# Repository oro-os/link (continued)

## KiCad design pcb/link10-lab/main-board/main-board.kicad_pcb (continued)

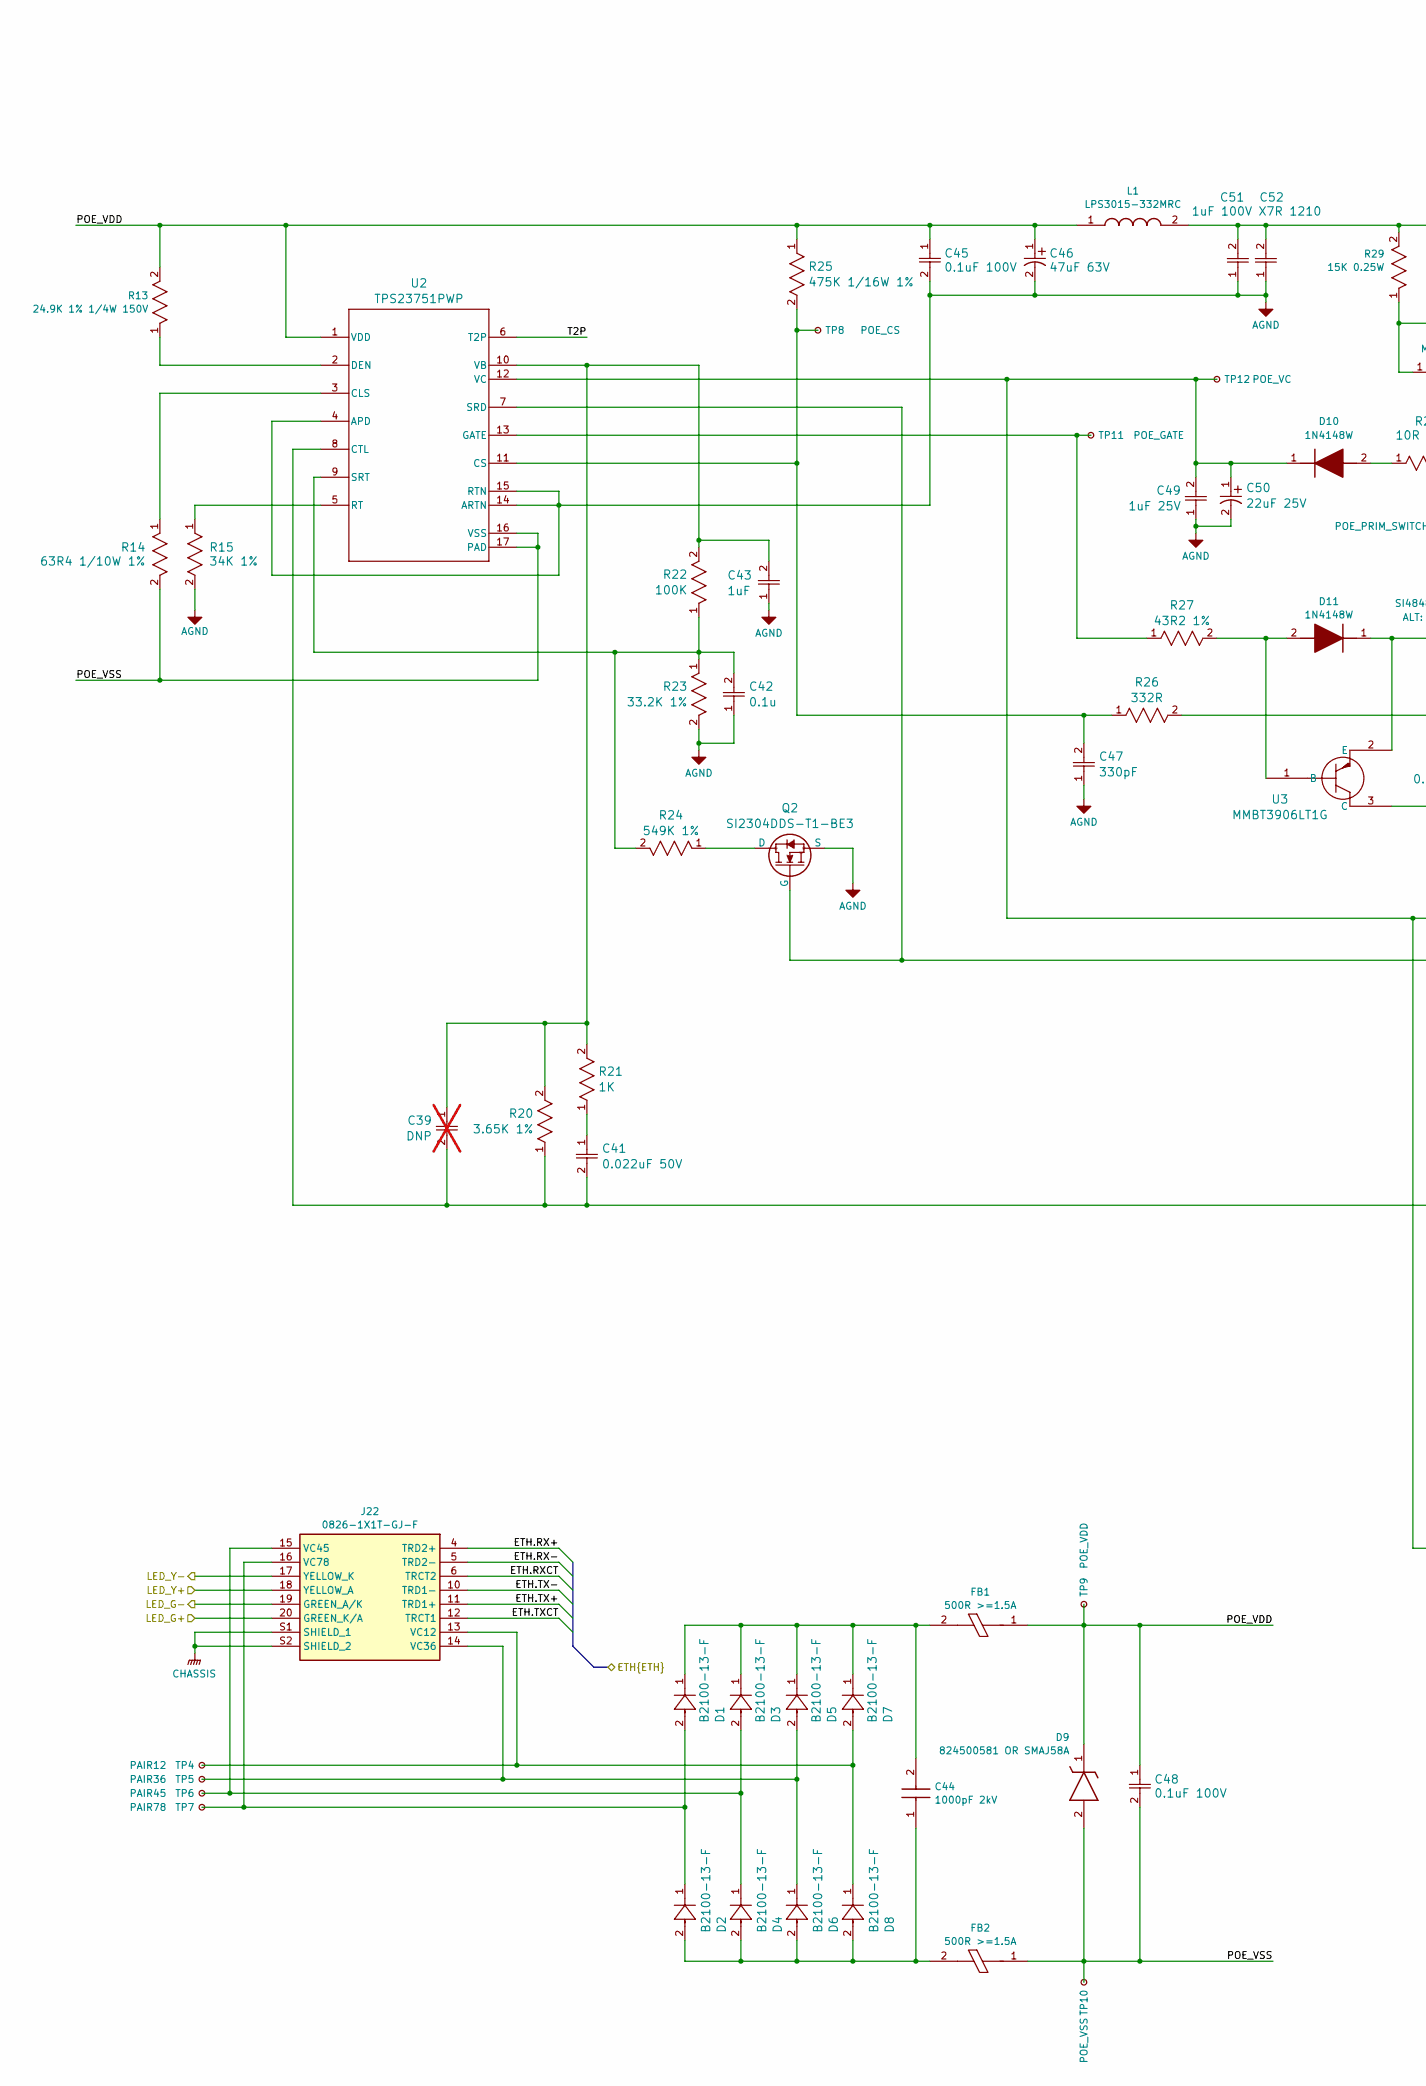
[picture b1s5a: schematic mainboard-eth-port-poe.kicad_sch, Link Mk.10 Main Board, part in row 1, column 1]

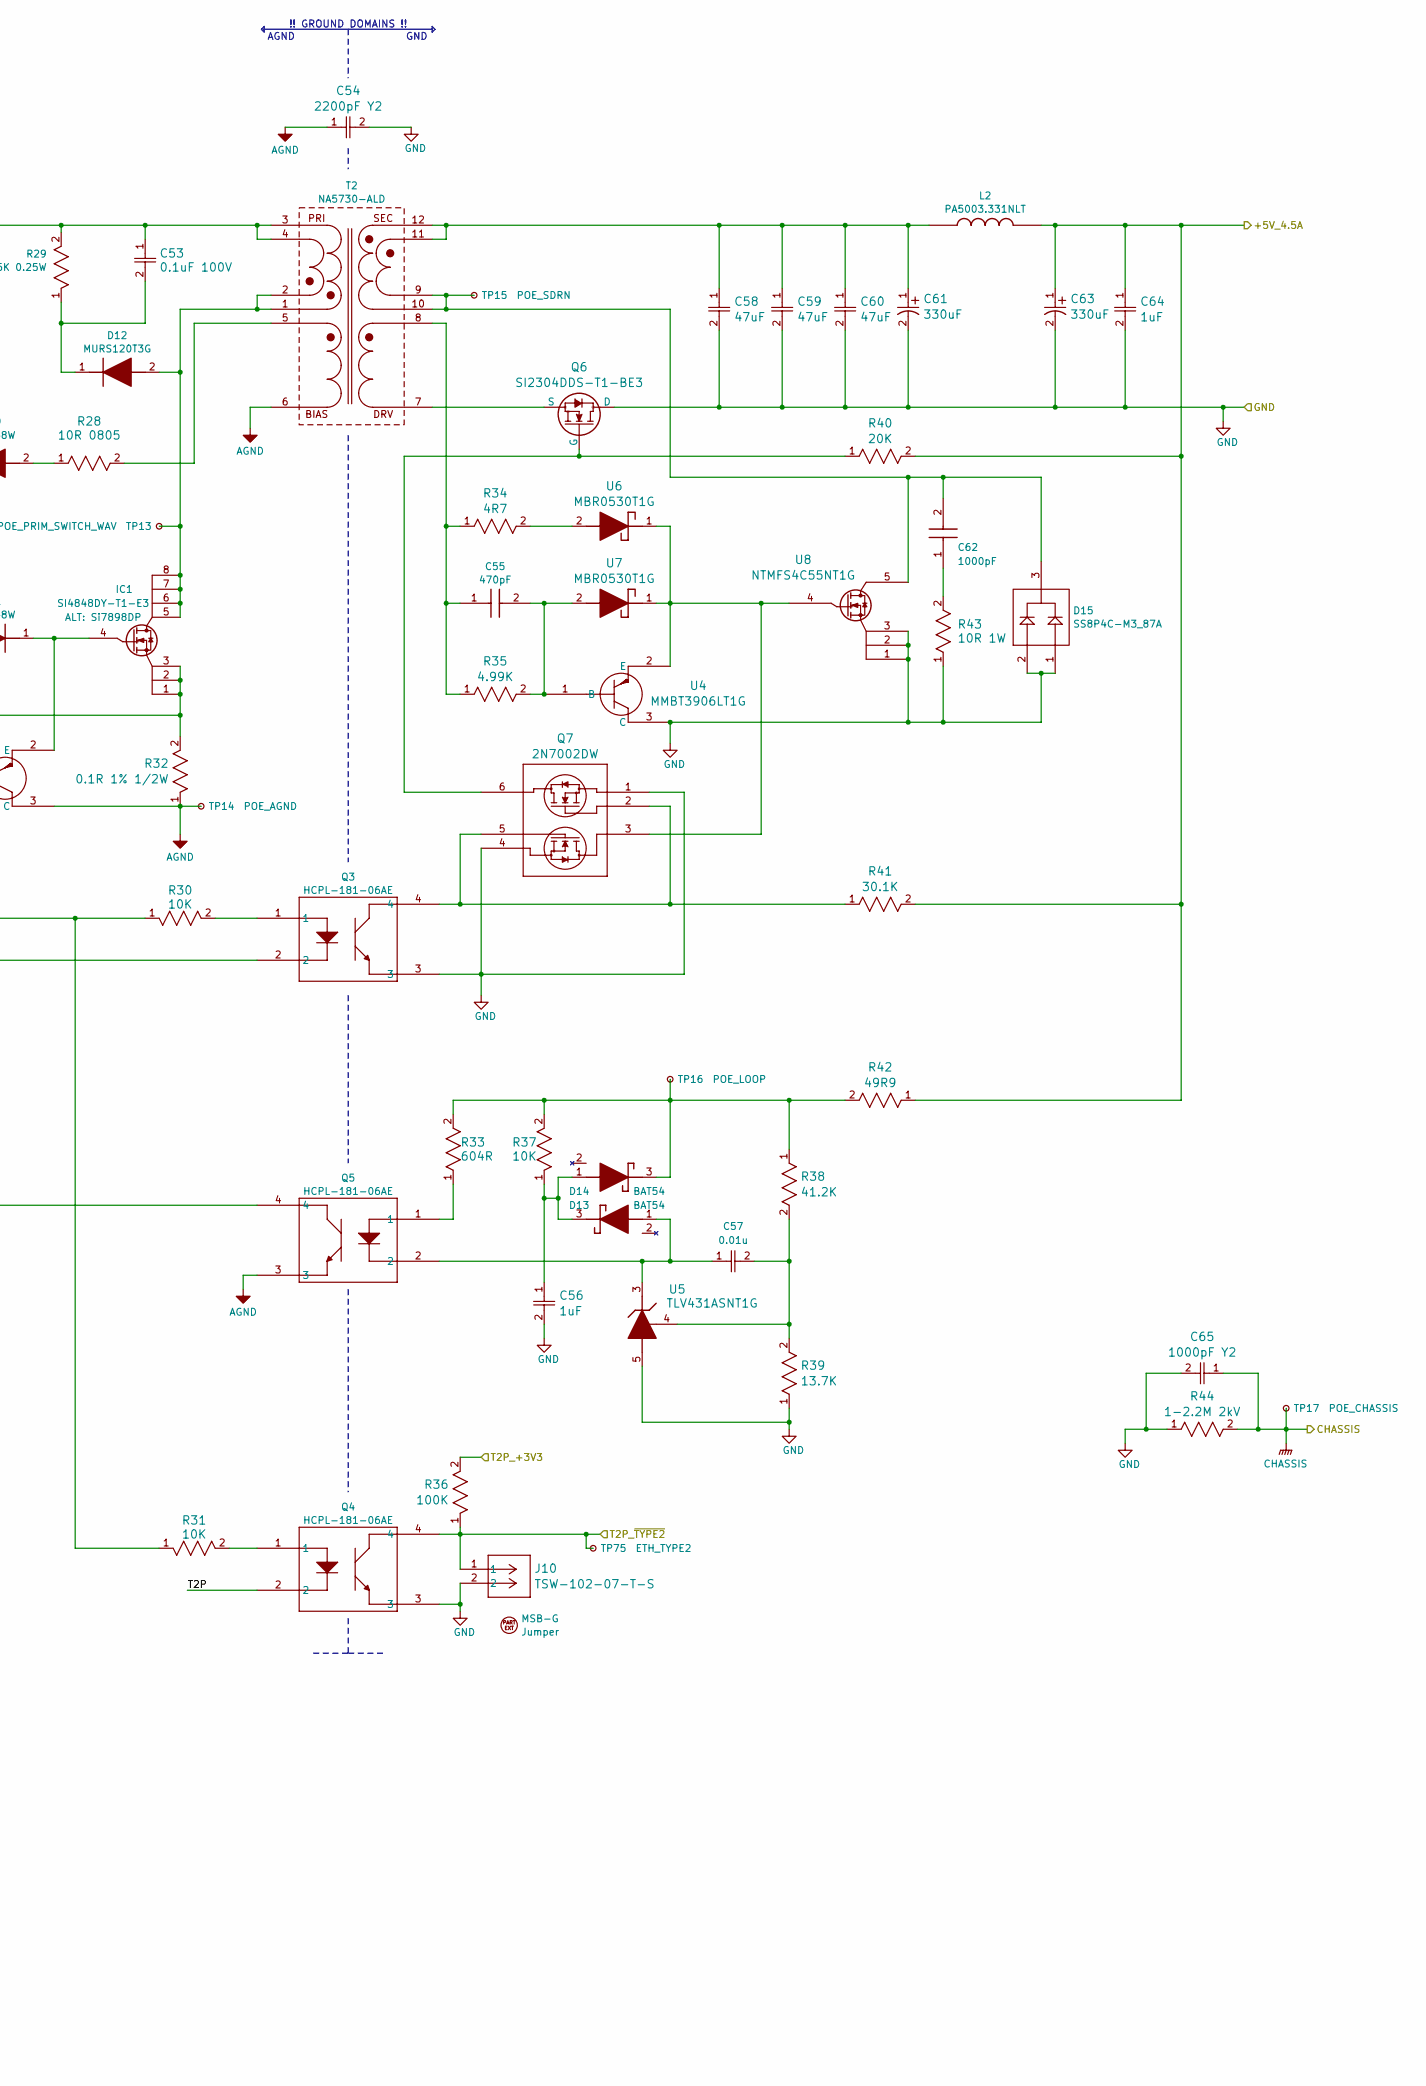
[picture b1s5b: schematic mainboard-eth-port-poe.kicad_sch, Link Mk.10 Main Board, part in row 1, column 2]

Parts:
C39: DNP; C_0603_1608Metric; not fitted
C41: 0.022uF 50V; OP_00069; Mouser P/N 810-CGA3E2X7R1H223K; Digi-Key P/N 445-5663-1-ND, 445-5663-2-ND, 445-5663-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
C42: 0.1u; OP_0001Y; DigiKey ID 587-MSAST1L3YB5104KFNA01CT-ND
C43: 1uF; OP_0005T
C44: 1000pF 2kV; OP_0000R; Manufacturer_Part_Number 885342210004; Mouser Part Number 710-885342210004
C45, C48, C53: 0.1uF 100V; OP_0005M; Mouser P/N 187-CL21B104KCFSFNE; Digi-Key P/N 1276-2923-1-ND, 1276-2923-2-ND, 1276-29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
C46: 47uF 63V; OP_0005N
C47: 330pF; OP_00068
C49: 1uF 25V; OP_0005T
C50: 22uF 25V; OP_0005V
C51, C52: 1uF 100V X7R 1210; OP_0005L
C54: 2200pF Y2; OP_0006U; Mouser P/N 710-8853522130151; Digi-Key P/N 732-8853522130151CT-ND, 732-88535221301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
C55: 470pF; OP_0006Q; Manufacturer_Part_Number C0603C471K5RAC; Mouser Part Number 80-C0603C471K5RAC
C56, C64: 1uF; OP_00001; Mouser P/N 581-0603YD105K; Digi-Key P/N 478-KGM15BR51C105KTCT-ND, 478-KGM15BR51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
C57: 0.01u; OP_0005C; Manufacturer_Part_Number C0603C103J2RECAUTO7411; Mouser Part Number 80-C0603C103J2REAULR
C58, C59, C60: 47uF; OP_0006G; Mouser P/N 963-LMK325BJ476KMHP; Digi-Key P/N 587-6341-1-ND, 587-6341-2-ND, 587-6341-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
C61, C63: 330uF; OP_0006H; Mouser P/N 667-EEE-FK0J331XP; Digi-Key P/N PCE3768CT-ND, PCE3768DKR-ND, PCE3768TR-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
C62: 1000pF; OP_0000R; Manufacturer_Part_Number 885342210004; Mouser Part Number 710-885342210004
C65: 1000pF Y2; OP_0006V; Mouser P/N 710-8853522130111; Digi-Key P/N 732-8853522130111CT-ND, 732-88535221301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
D1, D2, D3, D4, D5, D6, D7, D8: B2100-13-F; OP_0005E
D9: 824500581 OR SMAJ58A; OP_0005G; Manufacturer_Part_Number 824500581; Mouser Part Number 710-824500581
D10, D11: 1N4148W; OP_0005S; Manufacturer_Part_Number 1N4148W; Mouser Part Number 637-1N4148W
D12: MURS120T3G; OP_0005P; Manufacturer_Part_Number MURS120T3G; Mouser Part Number 863-MURS120T3G
D13, D14: BAT54; OP_0006I; Manufacturer_Part_Number BAT54; Mouser Part Number 637-BAT54
D15: SS8P4C-M3_87A; OP_0006E; Manufacturer_Part_Number SS8P4C-M3/87A; Mouser Part Number 625-SS8P4C-M3/87A
EXT2: MSB-G; Mouser P/N 737-MSB-G; Digi-Key P/N 2057-MSB-G-ND
FB1, FB2: 500R >=1.5A; OP_0005F; Manufacturer_Part_Number NFZ2MSD501SZ10L; Mouser Part Number 81-NFZ2MSD501SZ10L
IC1: SI4848DY-T1-E3; OP_0005R; Manufacturer_Part_Number SI4848DY-T1-E3; Mouser Part Number 781-SI4848DY-T1-E3
J10: TSW-102-07-T-S; OP_00079; Mouser P/N 200-TSW10207TS; Digi-Key P/N 612-TSW-102-07-T-S-ND
J22: 0826-1X1T-GJ-F; OP_0007O; Manufacturer_Part_Number 0826-1X1T-GJ-F; Mouser Part Number 530-0826-1X1T-GJ-F
L1: LPS3015-332MRC; OP_0005I; Manufacturer_Part_Number LPS3015-332MRC; Mouser Part Number 994-LPS3015-332MRC
L2: PA5003.331NLT; OP_0006F; Mouser P/N 673-PA5003.331NLT; Digi-Key P/N 553-4080-1-ND, 553-4080-2-ND, 553-4080-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
Q2, Q6: SI2304DDS-T1-BE3; OP_00063
Q3, Q4, Q5: HCPL-181-06AE; OP_00062; Manufacturer_Part_Number HCPL-181-06AE; Mouser Part Number 630-HCPL-181-06AE
Q7: 2N7002DW; OP_0006D; Mouser P/N 512-2N7002DW; Digi-Key P/N 2N7002DWCT-ND, 2N7002DWDKR-ND, 2N7002DW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
R13: 24.9K 1% 1/4W 150V; OP_0005H; Manufacturer_Part_Number CR1206-FX-2492ELF; Mouser Part Number 652-CR1206FX-2492ELF
R14: 63R4 1/10W 1%; OP_0005W
R15: 34K 1%; OP_0005X
R20: 3.65K 1%; OP_0006A; Mouser P/N 71-CRCW0603-3.65K-E3; Digi-Key P/N 541-3.65KHCT-ND, 541-3.65KHDKR-ND, 541-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
R21: 1K; OP_0003D
R22, R36: 100K; OP_00066
R23: 33.2K 1%; OP_00065
R24: 549K 1%; OP_00064; Mouser P/N 71-CRCW0603549KFKEAH; Digi-Key P/N CRCW0603549KFKEAHP-ND
R25: 475K 1/16W 1%; OP_0005Q; Manufacturer_Part_Number RC0603FR-07475KL; Mouser Part Number 603-RC0603FR-07475KL
R26: 332R; OP_00067
R27: 43R2 1%; OP_0005Y
R28: 10R 0805; OP_0005U
R29: 15K 0.25W; OP_0005O; Manufacturer_Part_Number RK73H2BTTD1502F; Mouser Part Number 660-RK73H2BTTD1502F
R30, R31, R37: 10K; OP_00021; DigiKey ID RMCF0402FT10K0CT-ND
R32: 0.1R 1% 1/2W; OP_00060
R33: 604R; OP_0006K; Mouser P/N 667-ERA-3AEB6040V, ERA-3AEB6040V; Digi-Key P/N P604DBCT-ND, P604DBDKR-ND, P604DBTR-ND
R34: 4R7; OP_0006O; Mouser P/N 594-MCT06030C4708FP5; Digi-Key P/N 749-1657-1-ND, 749-1657-2-ND, 749-1657-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
R35: 4.99K; OP_0006P; Mouser P/N 603-RT0603BRD074K99L; Digi-Key P/N YAG1678CT-ND, YAG1678DKR-ND, YAG1678TR-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
R38: 41.2K; OP_0006J; Mouser P/N 594-MCT06030C4122FP5; Digi-Key P/N 749-MCT06030C4122FP500CT-ND, 749-MCT060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
R39: 13.7K; OP_0006M; Mouser P/N 594-MCT0603MD1372DP5; Digi-Key P/N 749-MCT0603MD1372DP500CT-ND, 749-MCT060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
R40: 20K; OP_0006R; Mouser P/N 603-RT0603BRD0720KL; Digi-Key P/N YAG1582CT-ND, YAG1582DKR-ND, YAG1582TR-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
R41: 30.1K; OP_0006S; Mouser P/N 279-CPF0603F30K1C1; Digi-Key P/N A102260CT-ND, A102260DKR-ND, A102260TR-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
R42: 49R9; OP_00023; Mouser P/N 603-RT0402FRE0749R9L; Mouser URL null
R43: 10R 1W; OP_0006N; Mouser P/N 754-CPA2512Q10R0FST; Digi-Key P/N CPA25Q10.0CT-ND, CPA25Q10.0DKR-ND, CPA2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
R44: 1-2.2M 2kV; OP_0006W; Mouser P/N 652-CHV2512JW105ELF; Digi-Key P/N 118-CHV2512-JW-105ELFCT-ND, 118-CHV2512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
T2: NA5730-ALD; OP_0005J; Manufacturer_Part_Number NA5730-ALD; Mouser Part Number 994-NA5730-ALD
TP4: PAIR12; TestPoint_Pad_2.0x2.0mm
TP5: PAIR36; TestPoint_Pad_2.0x2.0mm
TP6: PAIR45; TestPoint_Pad_2.0x2.0mm
TP7: PAIR78; TestPoint_Pad_2.0x2.0mm
TP8: POE_CS; TestPoint_Pad_2.0x2.0mm
TP9: POE_VDD; TestPoint_Pad_2.0x2.0mm
TP10: POE_VSS; TestPoint_Pad_2.0x2.0mm
TP11: POE_GATE; TestPoint_Pad_2.0x2.0mm
TP12: POE_VC; TestPoint_Pad_2.0x2.0mm
TP13: POE_PRIM_SWITCH_WAV; TestPoint_Pad_2.0x2.0mm
TP14: POE_AGND; TestPoint_Pad_2.0x2.0mm
TP15: POE_SDRN; TestPoint_Pad_2.0x2.0mm
TP16: POE_LOOP; TestPoint_Pad_2.0x2.0mm
TP17: POE_CHASSIS; TestPoint_Pad_2.0x2.0mm
TP75: ETH_TYPE2; TestPoint_Pad_D1.0mm
U2: TPS23751PWP; OP_00057
U3, U4: MMBT3906LT1G; OP_0005Z
U5: TLV431ASNT1G; OP_0006L; Mouser P/N 863-TLV431ASNT1G; Digi-Key P/N TLV431ASNT1GOSCT-ND, TLV431ASNT1GOSDKR-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
U6, U7: MBR0530T1G; OP_0006B; Mouser P/N 863-MBR0530T1G; Digi-Key P/N MBR0530T1GOSCT-ND, MBR0530T1GOSDKR-ND, 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
U8: NTMFS4C55NT1G; OP_0006C; Mouser P/N 863-NTMFS4C55NT1G; Digi-Key P/N 488-NTMFS4C55NT1GCT-ND, 488-NTMFS4C55NT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

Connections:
+3V3_BASE: R36.2; also elsewhere on the board
+5V: C63.1, C64.1, L2.2, R40.2, R41.2, R42.1; also elsewhere on the board
/Baseboard/ETH_IS_TYPE2: J10.1, Q4.4, R36.1, TP75.1 (1_1); also elsewhere on the board
/CHASSIS: C65.1, J22.S1 (SHIELD_1), J22.S2 (SHIELD_2), R44.2, TP17.1 (1_1); also elsewhere on the board
/Ethernet Port + PoE/AGND: C42.1, C43.1, C45.2, C46.2, C47.1, C49.1, C50.2, C51.1, C52.1, C54.1, Q2.2 (S), Q5.3, R15.2, R23.2, R32.1, T2.6 (BIAS_2), TP14.1 (1_1), U2.4 (APD), U2.14 (ARTN), U2.15 (RTN), U3.3 (C)
/Ethernet Port + PoE/ETH.RX+: J22.4 (TRD2+); also elsewhere on the board
/Ethernet Port + PoE/ETH.RX-: J22.5 (TRD2-); also elsewhere on the board
/Ethernet Port + PoE/ETH.TX+: J22.11 (TRD1+); also elsewhere on the board
/Ethernet Port + PoE/ETH.TX-: J22.10 (TRD1-); also elsewhere on the board
/Ethernet Port + PoE/ETH.TXCT: J22.6 (TRCT2), J22.12 (TRCT1); also elsewhere on the board
/Ethernet Port + PoE/LED_G+: J22.20 (GREEN_K/A); also elsewhere on the board
/Ethernet Port + PoE/LED_G-: J22.19 (GREEN_A/K); also elsewhere on the board
/Ethernet Port + PoE/LED_Y+: J22.18 (YELLOW_A); also elsewhere on the board
/Ethernet Port + PoE/LED_Y-: J22.17 (YELLOW_K); also elsewhere on the board
/Ethernet Port + PoE/POE_VDD: C45.1, C46.1, C48.1, D9.1 (K), FB1.1, L1.1, R13.2, R25.1, TP9.1 (1_1), U2.1 (VDD)
/Ethernet Port + PoE/POE_VSS: C48.2, D9.2 (A), FB2.1, R14.2, TP10.1 (1_1), U2.16 (VSS), U2.17 (PAD)
/Ethernet Port + PoE/T2P: Q4.2, U2.6 (T2P)
GND: C54.2, C56.2, C58.2, C59.2, C60.2, C61.2, C63.2, C64.2, C65.2, D15.1 (A_1), D15.2 (A_2), J10.2, Q3.3, Q4.3, Q6.3 (D), Q7.1, Q7.4, R39.1, R43.1, R44.1, U4.3 (C), U5.5 (ANODE), U8.1 (SOURCE), U8.2 (SOURCE), U8.3 (SOURCE); also elsewhere on the board
unnamed: C41.1, R21.1
unnamed: C44.1, D2.2, D4.2, D6.2, D8.2, FB2.2
unnamed: C44.2, D1.1, D3.1, D5.1, D7.1, FB1.2
unnamed: C62.1, R43.2
unnamed: D10.2 (A), R28.1
unnamed: C49.2, C50.1, D10.1 (K), R30.1, R31.1, TP12.1 (1_1), U2.12 (VC)
unnamed: D11.2 (A), R27.2, U3.1 (B)
unnamed: D11.1 (K), IC1.4 (G), U3.2 (E)
unnamed: D12.2 (A), IC1.5 (D_1), IC1.6 (D_2), IC1.7 (D_3), IC1.8 (D_4), T2.1 (PRI_1_1), T2.2 (PRI_2_1), TP13.1 (1_1)
unnamed: C53.2, D12.1 (K), R29.1
unnamed: C57.1, D13.1 (A), Q5.2, U5.3 (CATHODE)
unnamed: C56.1, D13.3 (K), D14.1 (A), R37.1
unnamed: D14.3 (K), R33.2, R37.2, R38.1, R42.2, TP16.1 (1_1)
unnamed: C62.2, D15.3 (K), T2.9 (SEC_1_1), T2.10 (SEC_2_1), TP15.1 (1_1), U8.5 (DRAIN)
unnamed: IC1.1 (S_1), IC1.2 (S_2), IC1.3 (S_3), R26.2, R32.2
unnamed: D7.2, D8.1, J22.13 (VC12), TP4.1 (1_1)
unnamed: D5.2, D6.1, J22.14 (VC36), TP5.1 (1_1)
unnamed: D3.2, D4.1, J22.15 (VC45), TP6.1 (1_1)
unnamed: D1.2, D2.1, J22.16 (VC78), TP7.1 (1_1)
unnamed: Q2.3 (D), R24.1
unnamed: Q2.1 (G), Q3.2, U2.7 (SRD)
unnamed: Q3.1, R30.2
unnamed: Q3.4, Q7.2, Q7.5, R41.1
unnamed: Q4.1, R31.2
unnamed: Q5.1, R33.1
unnamed: Q6.1 (G), Q7.6, R40.1
unnamed: Q6.2 (S), T2.7 (DRIVE_1)
unnamed: R28.2, T2.5 (BIAS_1)
unnamed: C55.1, R34.1, R35.1, T2.8 (DRIVE_2)
unnamed: C51.2, C52.2, C53.1, L1.2, R29.2, T2.3 (PRI_1_2), T2.4 (PRI_2_2)
unnamed: C58.1, C59.1, C60.1, C61.1, L2.1, T2.11 (SEC_1_2), T2.12 (SEC_2_2)
unnamed: R14.1, U2.3 (CLS)
unnamed: C47.2, R25.2, R26.1, TP8.1 (1_1), U2.11 (CS)
unnamed: C39.2, C41.2, Q5.4, R20.1, U2.8 (CTL)
unnamed: R13.1, U2.2 (DEN)
unnamed: R27.1, TP11.1 (1_1), U2.13 (GATE)
unnamed: R15.1, U2.5 (RT)
unnamed: C42.2, R22.1, R23.1, R24.2, U2.9 (SRT)
unnamed: C39.1, C43.2, R20.2, R21.2, R22.2, U2.10 (VB)
unnamed: C55.2, R35.2, U4.1 (B), U7.2 (ANODE)
unnamed: Q7.3, U4.2 (E), U6.1 (CATHODE), U7.1 (CATHODE), U8.4 (GATE)
unnamed: C57.2, R38.2, R39.2, U5.4 (REFERENCE)
unnamed: R34.2, U6.2 (ANODE)

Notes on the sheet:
GND
!! GROUND DOMAINS !!
AGND

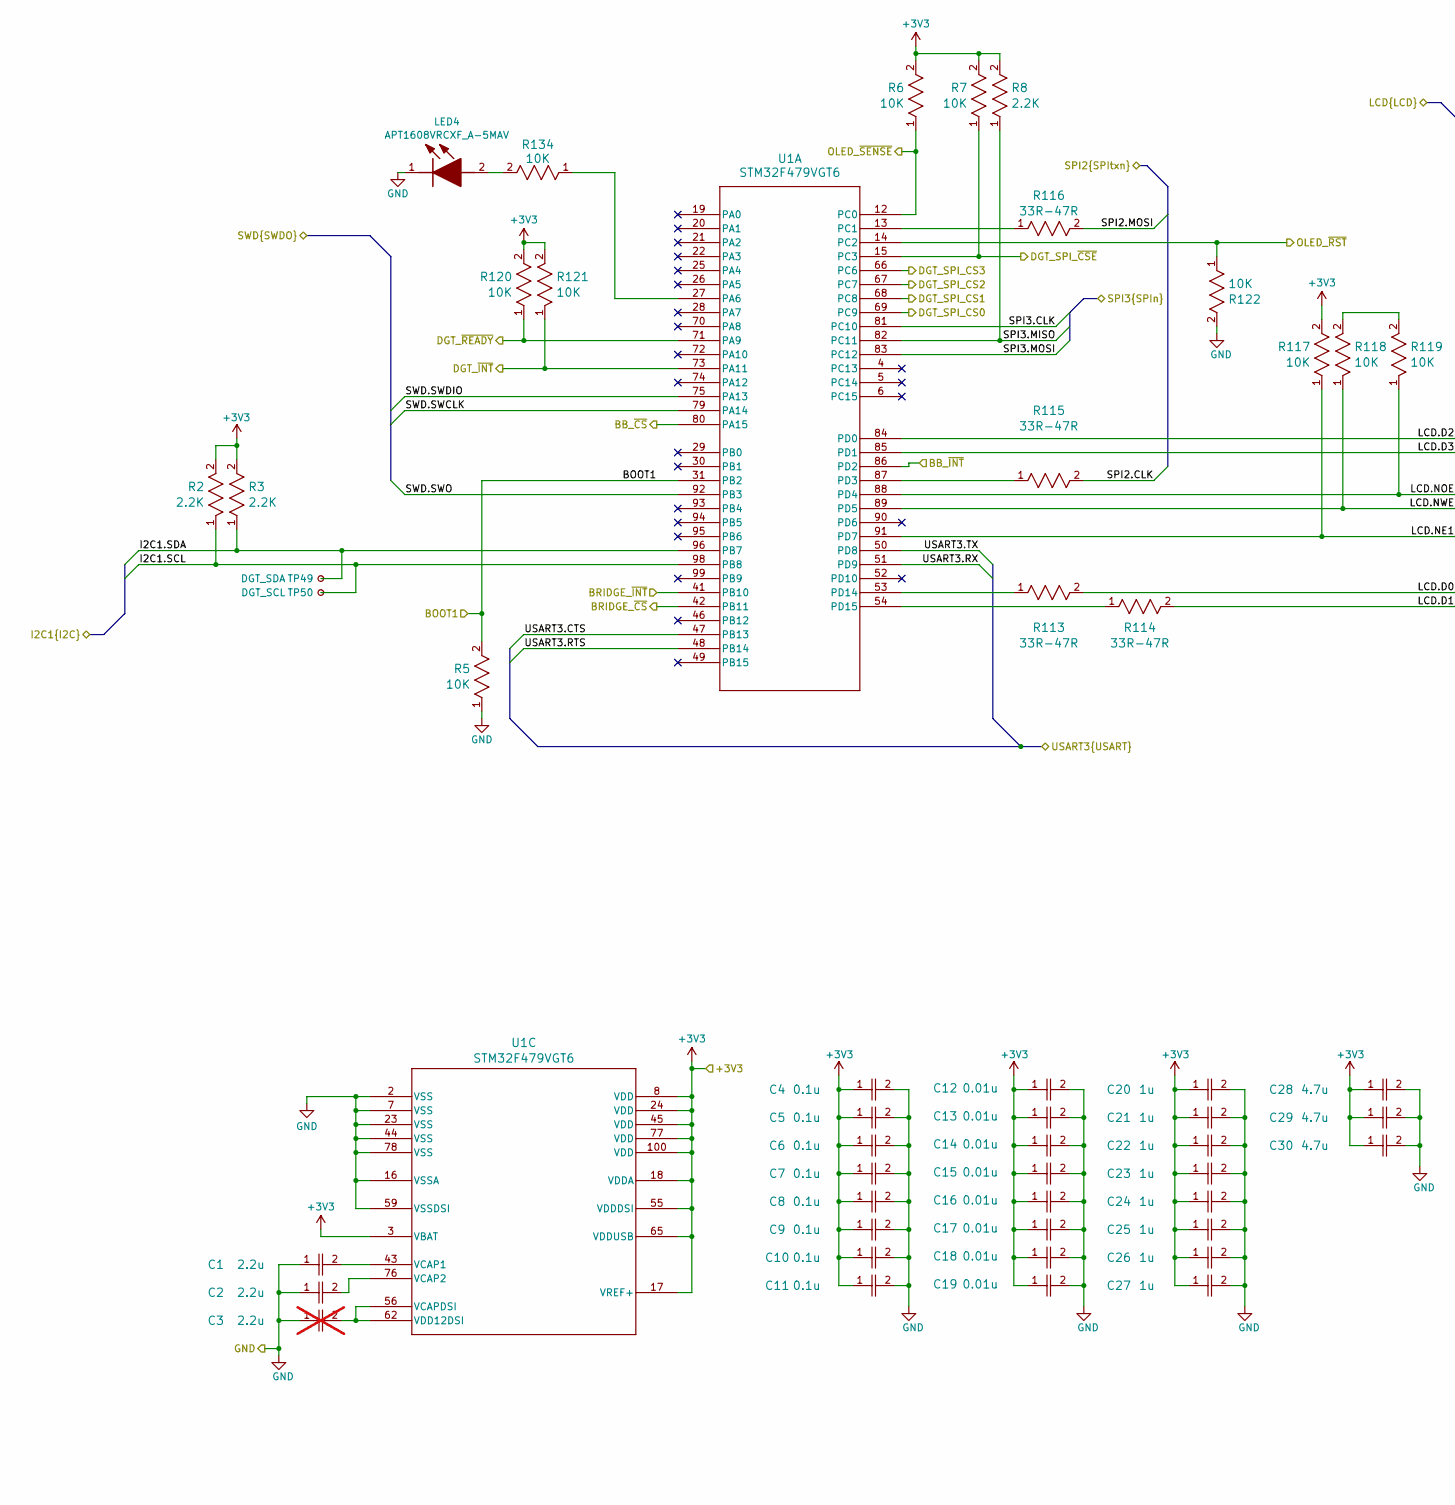
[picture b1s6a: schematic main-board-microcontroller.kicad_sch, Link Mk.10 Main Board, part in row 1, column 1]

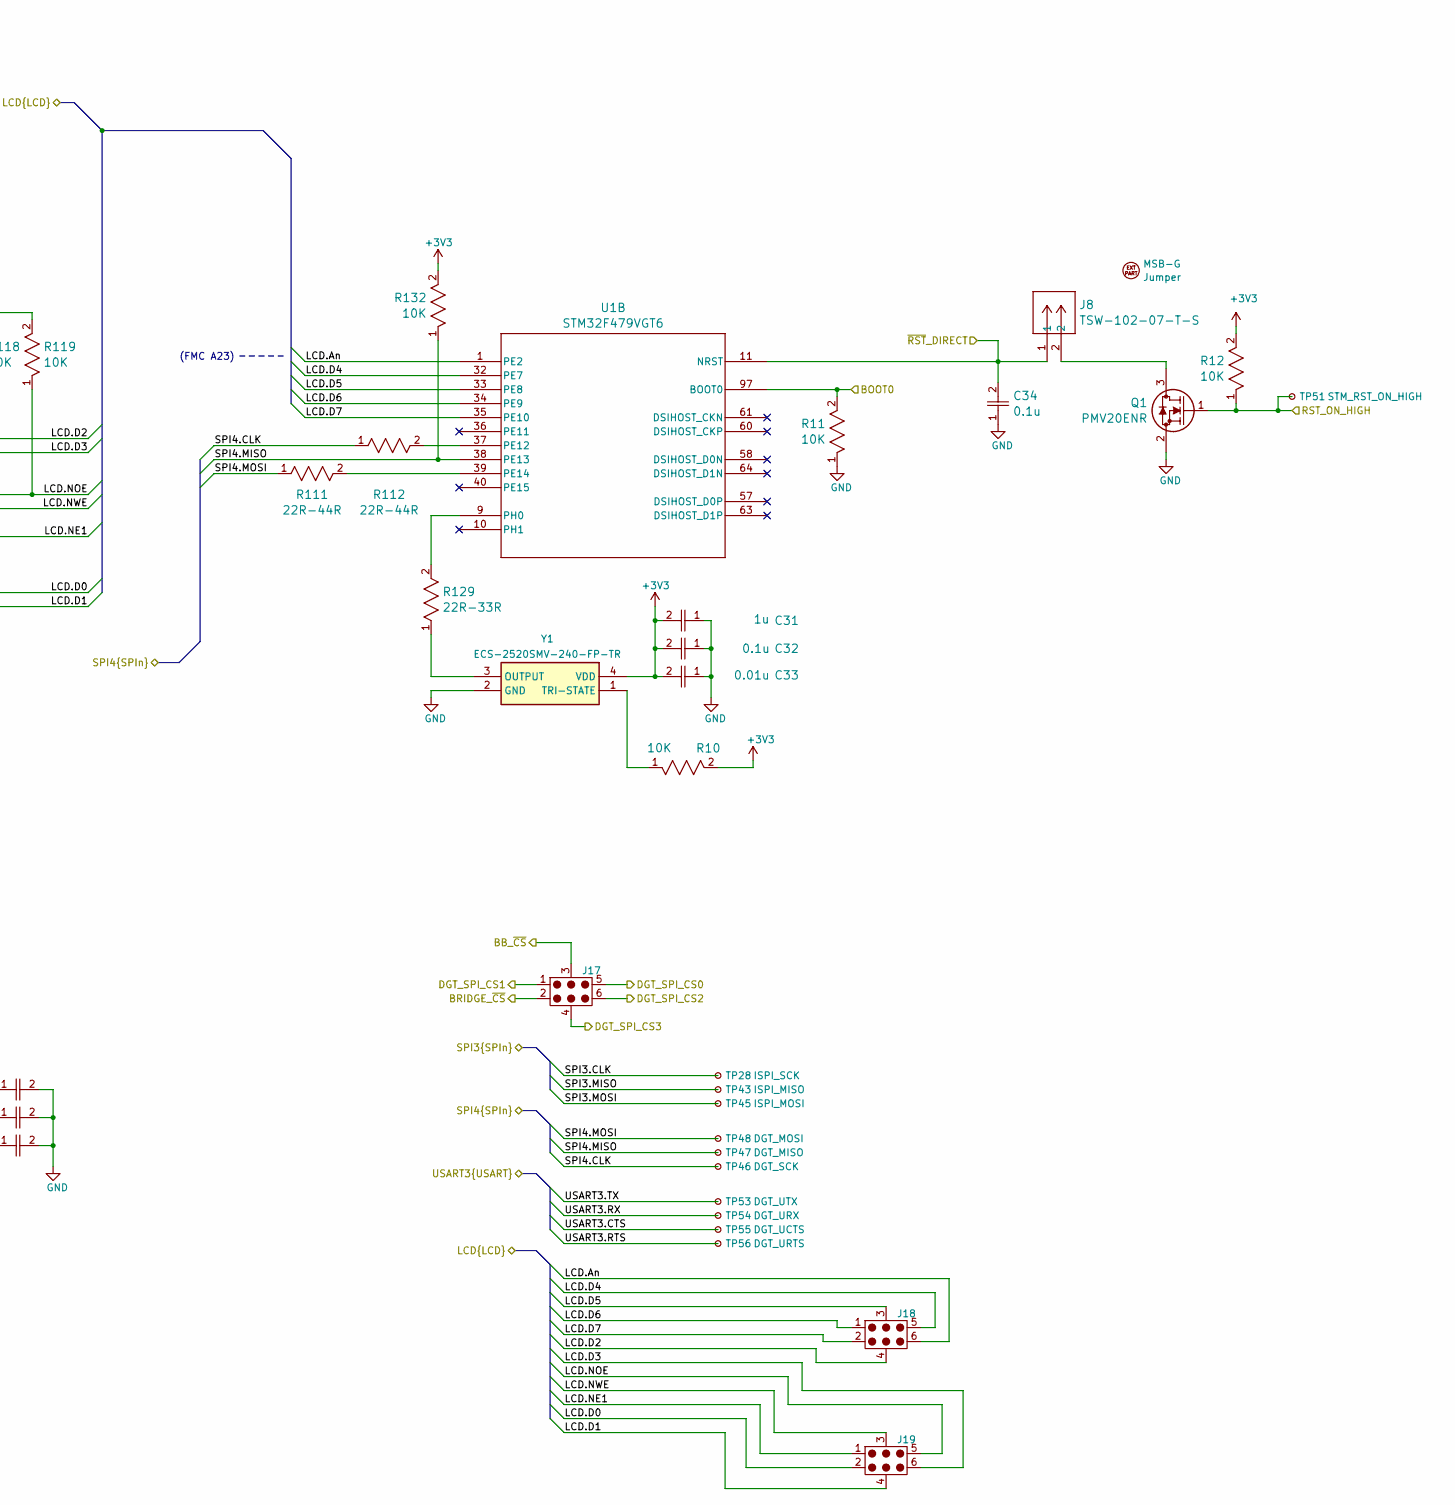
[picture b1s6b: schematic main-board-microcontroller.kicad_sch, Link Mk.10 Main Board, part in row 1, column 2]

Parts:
C1, C2: 2.2u; OP_0001G; Mouser ID 963-EMK105CC6225KV-F
C3: 2.2u; OP_0001G; Mouser ID 963-EMK105CC6225KV-F; not fitted
C4, C5, C6, C7, C8, C9, C10, C11, C32, C34: 0.1u; OP_0001Y; DigiKey ID 587-MSAST1L3YB5104KFNA01CT-ND
C12, C13, C14, C15, C16, C17, C18, C19, C33: 0.01u; OP_0000F; Mouser ID 791-0402B103J160CT
C20, C21, C22, C23, C24, C25, C26, C27, C31: 1u; OP_0001R; DigiKey ID 587-3766-1-ND
C28, C29, C30: 4.7u; OP_00014; Manufacturer_Part_Number GRM155C61E475ME15J; DigiKey ID 1276-1480-6-ND
EXT1: MSB-G; Mouser P/N 737-MSB-G; Digi-Key P/N 2057-MSB-G-ND
J8: TSW-102-07-T-S; OP_00079; Mouser P/N 200-TSW10207TS; Digi-Key P/N 612-TSW-102-07-T-S-ND
J17, J18, J19: CPG-81-TH-B-Pads; CPG-81-TH-B-Landing
LED4: APT1608VRCXF_A-5MAV; OP_0000U; Manufacturer_Part_Number APT1608VRCXF/A-5MAV; Mouser Part Number 604-APT1608VRCXF5MAV
Q1: PMV20ENR; OP_0001Z; DigiKey ID 1727-2301-1-ND
R2, R3, R8: 2.2K; OP_0002S; Mouser P/N 667-ERJ-P06F2321V; Digi-Key P/N ERJ-P06F2321V-ND
R5, R6, R7, R10, R11, R12, R117, R118, R119, R120, R121, R122, R132, R134: 10K; OP_00021; DigiKey ID RMCF0402FT10K0CT-ND
R111, R112: 22R-44R; OP_0005Y; Mouser P/N 652-CR0603FX-43R2ELF; Digi-Key P/N CR0603-FX-43R2ELFCT-ND, CR0603-FX-43R2E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
R113, R114, R115, R116: 33R-47R; OP_0005Y; Mouser P/N 652-CR0603FX-43R2ELF; Digi-Key P/N CR0603-FX-43R2ELFCT-ND, CR0603-FX-43R2E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
R129: 22R-33R; OP_00022; Mouser P/N 754-RR0510R-330D; DigiKey ID RR05R33DCT-ND
TP28: ISPI_SCK; TestPoint_Pad_D1.0mm
TP43: ISPI_MISO; TestPoint_Pad_D1.0mm
TP45: ISPI_MOSI; TestPoint_Pad_D1.0mm
TP46: DGT_SCK; TestPoint_Pad_D1.0mm
TP47: DGT_MISO; TestPoint_Pad_D1.0mm
TP48: DGT_MOSI; TestPoint_Pad_D1.0mm
TP49: DGT_SDA; TestPoint_Pad_D1.0mm
TP50: DGT_SCL; TestPoint_Pad_D1.0mm
TP51: STM_RST_ON_HIGH; TestPoint_Pad_D1.0mm
TP53: DGT_UTX; TestPoint_Pad_D1.0mm
TP54: DGT_URX; TestPoint_Pad_D1.0mm
TP55: DGT_UCTS; TestPoint_Pad_D1.0mm
TP56: DGT_URTS; TestPoint_Pad_D1.0mm
U1: STM32F479VGT6; OP_00028; Mouser ID 511-STM32F479VGT6
Y1: ECS-2520SMV-240-FP-TR; OP_0001E; Manufacturer_Part_Number ECS-2520SMV-240-FP-TR; Mouser Part Number 520-2520SMV-240-FP-T

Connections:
+3V3_STM: C4.1, C5.1, C6.1, C7.1, C8.1, C9.1, C10.1, C11.1, C12.1, C13.1, C14.1, C15.1, C16.1, C17.1, C18.1, C19.1, C20.1, C21.1, C22.1, C23.1, C24.1, C25.1, C26.1, C27.1, C28.1, C29.1, C30.1, C31.2, C32.2, C33.2, R2.2, R3.2, R6.2, R7.2, R8.2, R10.2, R12.2, R117.2, R120.2, R121.2, R132.2, U1.3 (VBAT), U1.8 (VDD), U1.17 (VREF+), U1.18 (VDDA), U1.24 (VDD), U1.45 (VDD), U1.55 (VDDDSI), U1.65 (VDDUSB), U1.77 (VDD), U1.100 (VDD), Y1.4 (VDD); also elsewhere on the board
/BRIDGE_INT: U1.41 (PB10); also elsewhere on the board
/Baseboard/BB_STM_~INT: U1.86 (PD2); also elsewhere on the board
/Baseboard/SPI1.CLK: TP28.1 (1_1), U1.81 (PC10); also elsewhere on the board
/Baseboard/SPI1.MISO: R8.1, TP43.1 (1_1), U1.82 (PC11); also elsewhere on the board
/Baseboard/SPI1.MOSI: TP45.1 (1_1), U1.83 (PC12); also elsewhere on the board
/Baseboard/SPI_~CS: J17.3, U1.80 (PA15); also elsewhere on the board
/Baseboard/STM32_RST: Q1.1 (G), R12.1, TP51.1 (1_1); also elsewhere on the board
/Bridge (RP) + SD/STM_SPI_~CS: J17.2, U1.42 (PB11); also elsewhere on the board
/DGT_INT: R121.1, U1.73 (PA11); also elsewhere on the board
/DGT_READY: R120.1, U1.71 (PA9); also elsewhere on the board
/DGT_SPI_CSE: R7.1, U1.15 (PC3); also elsewhere on the board
/MASTER_BOOT0: R11.2, U1.97 (BOOT0); also elsewhere on the board
/MASTER_BOOT1: R5.2, U1.31 (PB2); also elsewhere on the board
/MASTER_DIRECT_RST: C34.2, J8.1, U1.11 (NRST); also elsewhere on the board
/MASTER_SWD.SWCLK: U1.79 (PA14); also elsewhere on the board
/MASTER_SWD.SWDIO: U1.75 (PA13); also elsewhere on the board
/MASTER_SWD.SWO: U1.92 (PB3); also elsewhere on the board
/Microcontroller/DGT_SPI_CS0: J17.5, U1.69 (PC9); also elsewhere on the board
/Microcontroller/DGT_SPI_CS1: J17.1, U1.68 (PC8); also elsewhere on the board
/Microcontroller/DGT_SPI_CS2: J17.6, U1.67 (PC7); also elsewhere on the board
/Microcontroller/DGT_SPI_CS3: J17.4, U1.66 (PC6); also elsewhere on the board
/Microcontroller/I2C1.SCL: R2.1, TP50.1 (1_1), U1.98 (PB8); also elsewhere on the board
/Microcontroller/I2C1.SDA: R3.1, TP49.1 (1_1), U1.96 (PB7); also elsewhere on the board
/Microcontroller/LCD.An: J18.6, U1.1 (PE2); also elsewhere on the board
/Microcontroller/LCD.D2: J18.4, U1.84 (PD0); also elsewhere on the board
/Microcontroller/LCD.D3: J19.6, U1.85 (PD1); also elsewhere on the board
/Microcontroller/LCD.D4: J18.5, U1.32 (PE7); also elsewhere on the board
/Microcontroller/LCD.D5: J18.3, U1.33 (PE8); also elsewhere on the board
/Microcontroller/LCD.D6: J18.1, U1.34 (PE9); also elsewhere on the board
/Microcontroller/LCD.D7: J18.2, U1.35 (PE10); also elsewhere on the board
/Microcontroller/LCD.NE1: J19.1, R117.1, U1.91 (PD7); also elsewhere on the board
/Microcontroller/LCD.NOE: J19.5, R119.1, U1.88 (PD4); also elsewhere on the board
/Microcontroller/LCD.NWE: J19.3, R118.1, U1.89 (PD5); also elsewhere on the board
/Microcontroller/SPI2.CLK: J19.2, R113.2, R115.2; also elsewhere on the board
/Microcontroller/SPI2.MOSI: J19.4, R114.2, R116.2; also elsewhere on the board
/Microcontroller/SPI4.CLK: R112.1, TP46.1 (1_1); also elsewhere on the board
/Microcontroller/SPI4.MISO: R132.1, TP47.1 (1_1), U1.38 (PE13); also elsewhere on the board
/Microcontroller/SPI4.MOSI: R111.1, TP48.1 (1_1); also elsewhere on the board
/Microcontroller/USART3.CTS: TP55.1 (1_1), U1.47 (PB13); also elsewhere on the board
/Microcontroller/USART3.RTS: TP56.1 (1_1), U1.48 (PB14); also elsewhere on the board
/Microcontroller/USART3.RX: TP54.1 (1_1), U1.51 (PD9); also elsewhere on the board
/Microcontroller/USART3.TX: TP53.1 (1_1), U1.50 (PD8); also elsewhere on the board
/OLED_RST: R122.1, U1.14 (PC2); also elsewhere on the board
/OLED_SENSE: R6.1, U1.12 (PC0); also elsewhere on the board
GND: C1.1, C2.1, C3.1, C4.2, C5.2, C6.2, C7.2, C8.2, C9.2, C10.2, C11.2, C12.2, C13.2, C14.2, C15.2, C16.2, C17.2, C18.2, C19.2, C20.2, C21.2, C22.2, C23.2, C24.2, C25.2, C26.2, C27.2, C28.2, C29.2, C30.2, C31.1, C32.1, C33.1, C34.1, LED4.1 (K), Q1.2 (S), R5.1, R11.1, R122.2, U1.2 (VSS), U1.7 (VSS), U1.16 (VSSA), U1.23 (VSS), U1.44 (VSS), U1.59 (VSSDSI), U1.78 (VSS), Y1.2 (GND); also elsewhere on the board
unnamed: LED4.2 (A), R134.2
unnamed: J8.2, Q1.3 (D)
unnamed: R118.2, R119.2
unnamed: R134.1, U1.27 (PA6)
unnamed: R116.1, U1.13 (PC1)
unnamed: R115.1, U1.87 (PD3)
unnamed: R113.1, U1.53 (PD14)
unnamed: R114.1, U1.54 (PD15)
unnamed: R112.2, U1.37 (PE12)
unnamed: R111.2, U1.39 (PE14)
unnamed: R129.2, U1.9 (PH0)
unnamed: C1.2, U1.43 (VCAP1)
unnamed: C2.2, U1.76 (VCAP2)
unnamed: C3.2, U1.56 (VCAPDSI), U1.62 (VDD12DSI)
unnamed: R129.1, Y1.3 (OUTPUT)
unnamed: R10.1, Y1.1 (TRI-STATE)

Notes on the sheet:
(FMC A23)
